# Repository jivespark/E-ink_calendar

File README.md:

# E-ink_calendar
This is my project I made for the HackClub Blueprint YSWS. It is a calendar/ToDo tracker using an E-ink display, which can sit on your desk, and show you a calendar, and up to 5 tasks which you can mark as completed using 5 mechanical buttons next to the display.

To add tasks to the todo system you can send a message using a BLE terminal from any device.The first time you use it the time will probably be set incorrectly, and to set it you have to send `/tmst mmddhhmm` where the first mm means current month(like 03), dd is the current day(example: 09), hh is the current hour(for example 13), and the second mm is the minute(like 46). So if the time would be 2026, march 9th, 1:46 PM, you would send `/tmst 03091346`. Note that if the current year is not 2026 you will have to update the code.py file, and the 1.bin, 2.bin, ..., 12.bin files, but I will post the new versions in a new commit.

I mainly made this project to make use of the Blueprint YSWS, since it ends in a few weeks, and I wanted something cool. When thinking about project ideas I sudennly remembered someone building a little desktop habit tracker/To-do list, and thats where I started out of. I would like to give credit to the person who did the original device that gave me this idea, but i couldn't remember where I saw it. I also sometimes struggle with forgetting things that I should do, so i thought a device like this would help me, and potentially others with the same problem.

**Full assembly:**

You will need to use jumper wires to connect the display with the pcb. See this wiring diagram for more info(the yellow lines show what to connect with what):

**Schematic:**

**PCB:**

BOM:

|Item                                         |Description    |Quantity|Unit price($)(Including tax)|Total price($)(Including tax)|URL:                                                     |Running total:|
|---------------------------------------------|---------------|--------|----------------------------|-----------------------------|---------------------------------------------------------|--------------|
|XIAO nRF52840                                |Microcontroller|1       |13.72                       |13.72                        |https://www.aliexpress.com/item/1005008326858009.html    |13.72         |
|waveshare 800×480, 7.5inch E-Ink display     |Display        |1       |56.99                       |56.99                        |https://www.waveshare.com/product/7.5inch-e-paper-hat.htm|70.71         |
|10pcs XDA2 Keycaps                           |Keycaps        |10      |0.34                        |3.43                         |https://www.aliexpress.com/item/1005006910173774.html    |74,14         |
|Mechanical Keyboard Replacement Blue Switches|Keyswitches    |16      |0.19                        |3.14                         |https://www.aliexpress.com/item/1005011789237834.html    |77,28         |

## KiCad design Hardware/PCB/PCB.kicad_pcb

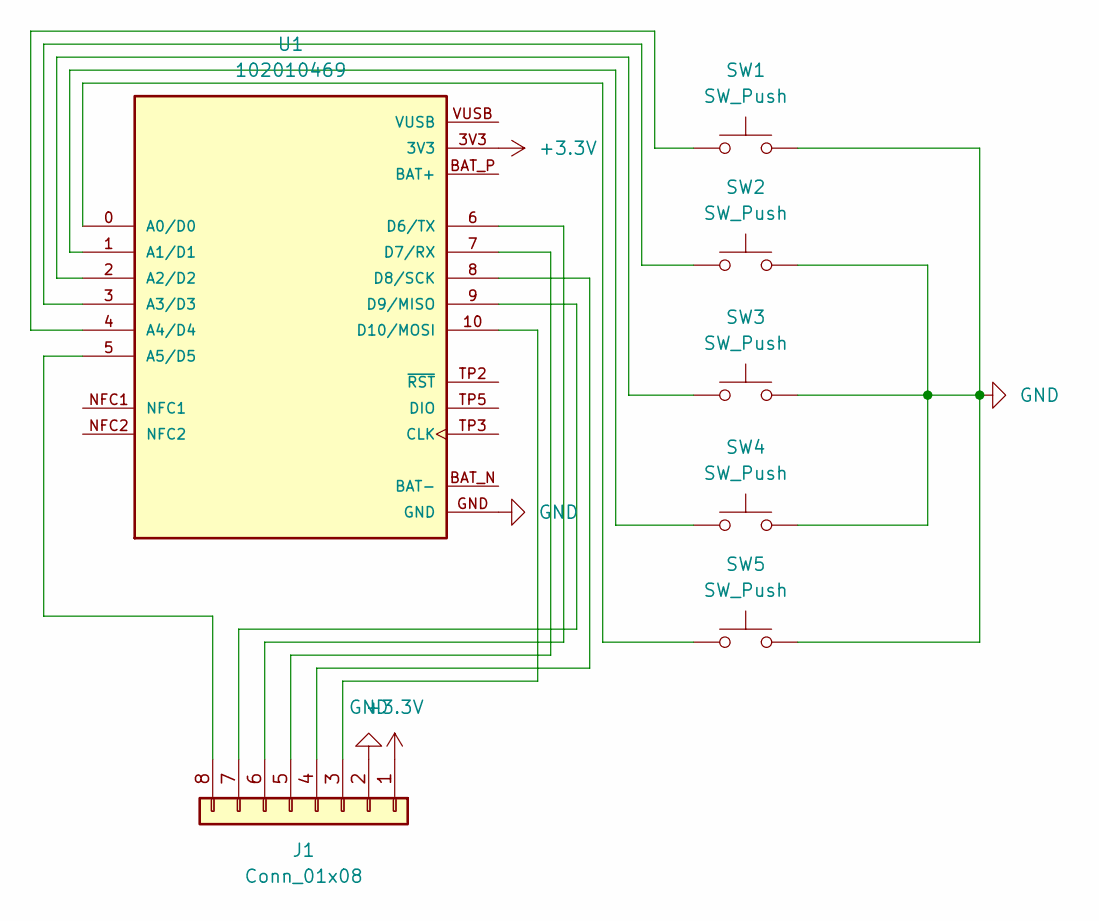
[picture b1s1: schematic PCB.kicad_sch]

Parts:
J1: Conn_01x08; PinHeader_1x08_P2.54mm_Vertical
SW1, SW2, SW3, SW4, SW5: SW_Push; SW_Cherry_MX_1.00u_PCB
U1: 102010469; MODULE_102010469; PARTREV 2/24/23

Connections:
+3.3V: J1.1, U1.3V3
GND: J1.2, SW1.2, SW2.2, SW3.2, SW4.2, SW5.2, U1.GND, U1.TP1 (GND)
unnamed: J1.3, U1.10 (D10/MOSI)
unnamed: J1.4, U1.8 (D8/SCK)
unnamed: J1.5, U1.7 (D7/RX)
unnamed: J1.6, U1.6 (D6/TX)
unnamed: J1.7, U1.9 (D9/MISO)
unnamed: J1.8, U1.5 (A5/D5)
unnamed: SW5.1, U1.0 (A0/D0)
unnamed: SW4.1, U1.1 (A1/D1)
unnamed: SW3.1, U1.2 (A2/D2)
unnamed: SW2.1, U1.3 (A3/D3)
unnamed: SW1.1, U1.4 (A4/D4)

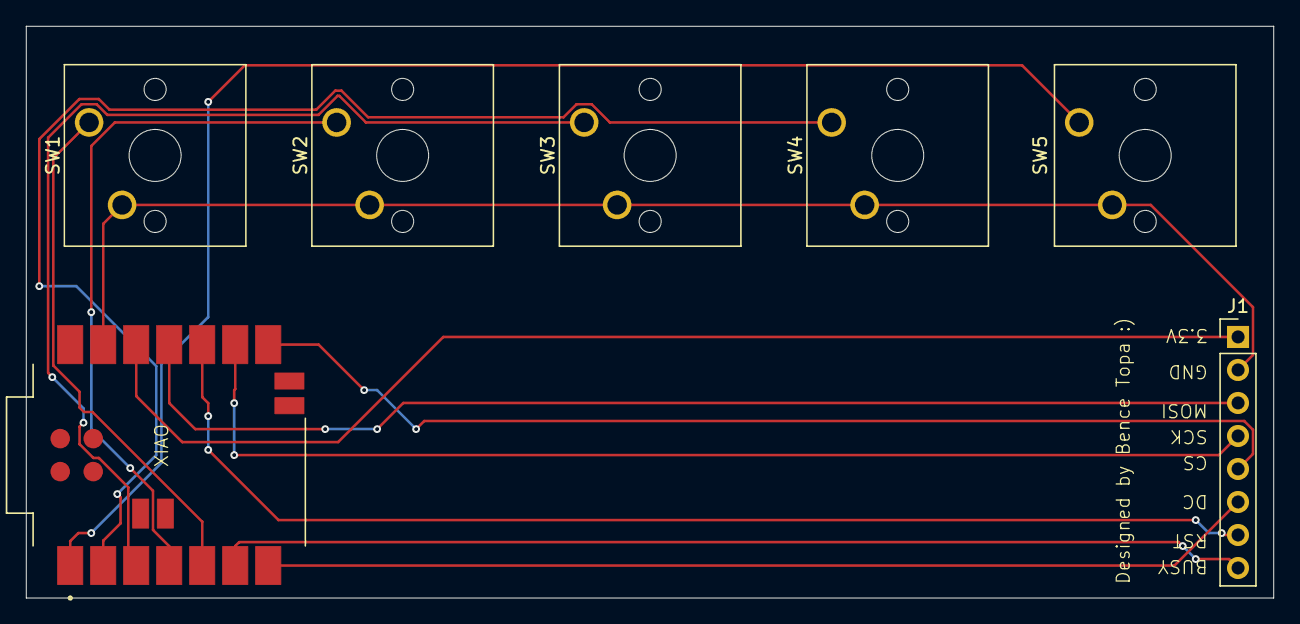
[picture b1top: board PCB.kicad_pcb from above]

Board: 2 copper layers, 96.0 x 44.0 mm, 7 parts (0 on the bottom side), 13 nets.

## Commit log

2026-03-14 Added project firmware, and hardware files
2026-03-14 Create Firmware-instructions.md with installation details
2026-03-14 Rename Firmware-instrucions.md to README.md to make it easier to find
2026-03-14 Update README with project details and instructions
2026-03-14 I added pictures for the readme
2026-03-14 Update README with additional project resources
2026-03-15 Added case files
2026-03-15 Added pictures for README
2026-03-15 Update README with assembly and wiring images
2026-03-15 Added the BOM
2026-03-15 Add BOM section to README
    Added a Bill of Materials (BOM) section with item details.
2026-03-15 Update BOM.csv to simplify URL for nRF52840
2026-03-15 Update BOM.csv with new items
2026-03-15 Update BOM table
2026-03-15 Fix formatting of price in README.md
